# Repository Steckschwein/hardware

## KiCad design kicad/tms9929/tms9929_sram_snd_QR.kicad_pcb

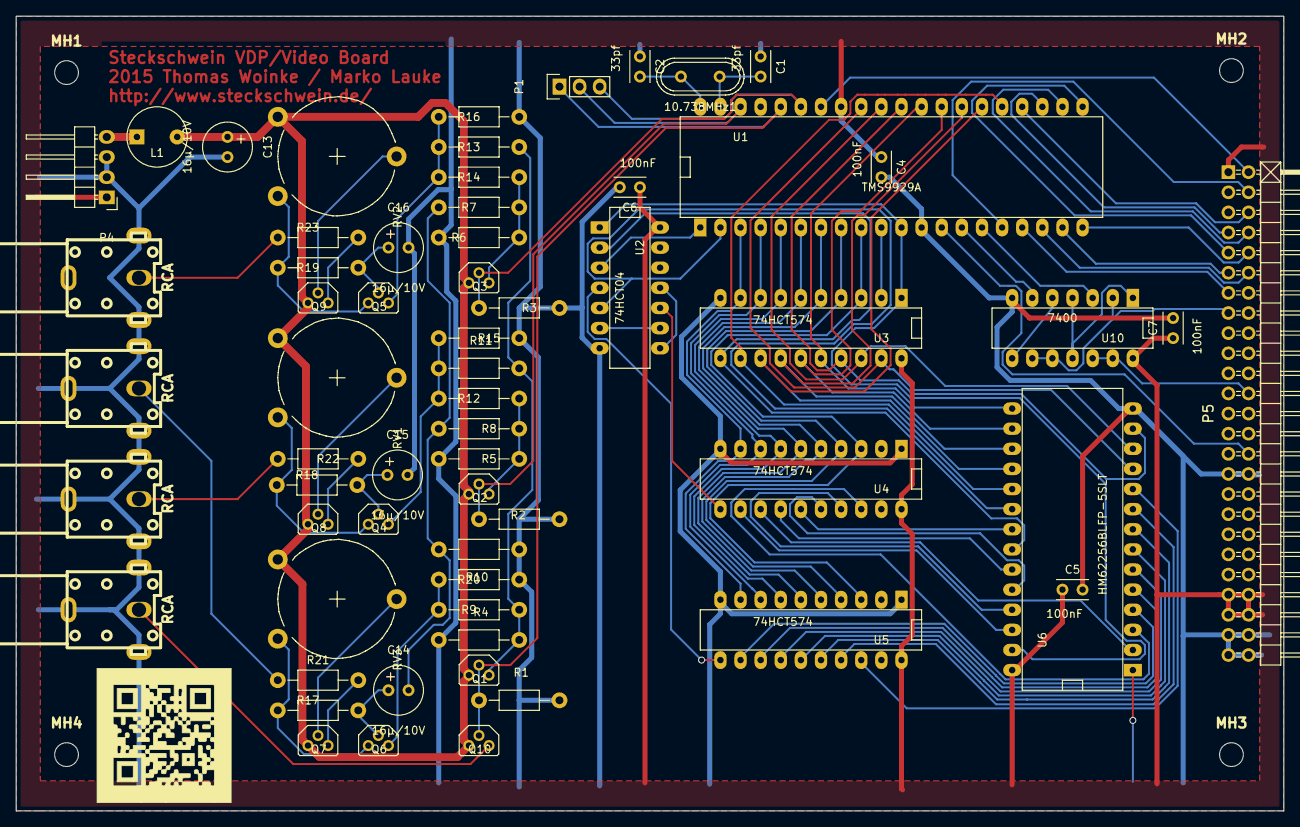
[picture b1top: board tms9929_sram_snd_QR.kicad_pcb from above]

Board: 2 copper layers, 160.0 x 100.3 mm, 66 parts (0 on the bottom side), 87 nets.

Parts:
10.738MHz1: CRYSTAL; Crystal_HC49-U_Vertical
Blue1: RCA; rca_black
C1, C2: 33pf; Capacitor4x3RM2.5
C4, C5, C6, C7: 100nF; Capacitor4x3RM2.5
C13, C14, C15, C16: 16µ/10V; Elko_vert_11.2x6.3mm_RM2.5
Green1: RCA; rca_black
L1: 47µH; INDUCTOR_V
MH1, MH2, MH3, MH4: MountingHole_3mm_RevA_Date21Jun2010; MountingHole_3mm
P1: CONN_01X03; Pin_Header_Straight_1x03
P4: Power; Pin_Header_Angled_1x04
P5: CONN_02X25; Pin_Header_Angled_2x25
Q1, Q2, Q3, Q4, Q5, Q6, Q7, Q8, Q9, Q10: BC550; TO92PN
R1, R2, R3: 470; Resistor_Horizontal_RM10mm
R4, R5, R6: 1K; Resistor_Horizontal_RM10mm
R7, R8, R9, R10, R11, R12, R13, R14, R15, R16, R20: 1K 1%; Resistor_Horizontal_RM10mm
R17, R18, R19: 100K; Resistor_Horizontal_RM10mm
R21, R22, R23: 100; Resistor_Horizontal_RM10mm
RV1, RV2, RV3: 5K; Potentiometer_Trimmer-Piher_PT15-V15_horizontal
Red1: RCA; rca_black
Sync1: RCA; rca_black
U1: TMS9929A; DIP-40__600_ELL
U2: 74HCT04; DIP-14__300_ELL
U3, U4, U5: 74HCT574; DIP-20__300_ELL
U6: HM62256BLFP-5SLT; DIP-28__600_ELL
U10: 7400; DIP-14__300_ELL

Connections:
+12V: L1.1, P4.4
/12VS: C13.1, L1.2, Q1.1, Q2.1, Q3.1, Q7.1, Q8.1, Q9.1, Q10.1, RV1.1, RV2.1, RV3.1
/50Pin/A0: P5.30, U1.13
/50Pin/D0: P5.13, U1.17
/50Pin/D1: P5.12, U1.18
/50Pin/D2: P5.11, U1.19
/50Pin/D3: P5.10, U1.20
/50Pin/D4: P5.9, U1.21
/50Pin/D5: P5.8, U1.22
/50Pin/D6: P5.7, U1.23
/50Pin/D7: P5.6, U1.24
/A0: U5.18, U6.10
/A1: U5.17, U6.9
/A2: U5.16, U6.8
/A3: U5.15, U6.7
/A4: U5.14, U6.6
/A5: U5.13, U6.5
/A6: U5.12, U6.4
/A7: U4.18, U6.3
/A8: U4.17, U6.25
/A9: U4.16, U6.24
/A10: U4.15, U6.21
/A11: U4.14, U6.23
/A12: U4.13, U6.2
/A13: U4.12, U6.26
/AD0: U1.10, U3.2
/AD1: U1.9, U3.3, U4.3, U5.3
/AD2: U1.8, U3.4, U4.4, U5.4
/AD3: U1.7, U3.5, U4.5, U5.5
/AD4: U1.6, U3.6, U4.6, U5.6
/AD5: U1.5, U3.7, U4.7, U5.7
/AD6: U1.4, U3.8, U4.8, U5.8
/AD7: U1.3, U3.9, U4.9, U5.9
/B-Y: P1.3, Q3.2, R3.1, U1.35
/CAS: U1.2, U2.5, U6.20
/COL: U2.10, U4.11
/CS_VDP: P5.24, U10.12, U10.13
/IRQ: P5.4, U1.16
/R-Y: P1.2, Q2.2, R2.1, U1.38
/RAS: U1.1, U2.3
/RD0: U1.32, U3.19, U6.11
/RD1: U1.31, U3.18, U6.12
/RD2: U1.30, U3.17, U6.13
/RD3: U1.29, U3.16, U6.15
/RD4: U1.28, U3.15, U6.16
/RD5: U1.27, U3.14, U6.17
/RD6: U1.26, U3.13, U6.18
/RD7: U1.25, U3.12, U6.19
/RESET: P5.2, U1.34
/RGB-B: Blue1.2, R23.1
/RGB-G: Green1.2, R21.1
/RGB-R: R22.1, Red1.2
/ROW: U2.4, U5.11
/RW: P5.15, U10.2, U10.9, U10.10
/SYNC: Q10.3, Sync1.2
/V_RW: U1.11, U2.1, U3.1, U6.27
/WR: U2.2, U3.11, U6.22
/Y: P1.1, Q1.2, Q10.2, R1.1, U1.36
GND: Blue1.1, C1.1, C2.1, C4.2, C5.2, C6.2, C7.2, C13.2, C15.2, C16.2, Green1.1, P4.2, P4.3, P5.31, P5.32, P5.35, P5.37, P5.47, P5.48, P5.49, P5.50, R1.2, R2.2, R3.2, R4.1, R5.1, R6.1, R10.1, R15.1, R16.1, R20.1, Red1.1, Sync1.1, U1.12, U2.7, U3.10, U4.1, U4.10, U5.1, U5.10, U6.1, U6.14, U10.7
unnamed: 10.738MHz1.1, C1.2, U1.39
unnamed: 10.738MHz1.2, C2.2, U1.40
unnamed: C14.1, Q6.2, R17.2
unnamed: C14.2, R7.1, R8.1, R10.2
unnamed: C15.1, Q4.2, R18.1
unnamed: C16.1, Q5.2, R19.1
unnamed: Q1.3, R4.2, R9.2, R11.2, R13.2
unnamed: Q2.3, R5.2, R8.2, R12.2
unnamed: Q3.3, R6.2, R7.2, R14.2
unnamed: Q4.1, R18.2, RV1.3
unnamed: Q4.3, R11.1, R12.1, R15.2
unnamed: Q5.1, R19.2, RV2.3
unnamed: Q5.3, R13.1, R14.1, R16.2
unnamed: Q6.1, R17.1, RV3.3
unnamed: Q6.3, R9.1, R20.2
unnamed: Q7.2, RV3.2
unnamed: Q7.3, R21.2
unnamed: Q8.2, RV1.2
unnamed: Q8.3, R22.2
unnamed: Q9.2, RV2.2
unnamed: Q9.3, R23.2
unnamed: U1.14, U10.6
unnamed: U1.15, U10.3
unnamed: U2.6, U2.9
unnamed: U2.8, U2.11
unnamed: U10.1, U10.4, U10.11
unnamed: U10.5, U10.8
VCC: C4.1, C5.1, C6.1, C7.1, P4.1, P5.1, P5.43, P5.44, P5.45, P5.46, U1.33, U2.14, U3.20, U4.20, U5.20, U6.28, U10.14

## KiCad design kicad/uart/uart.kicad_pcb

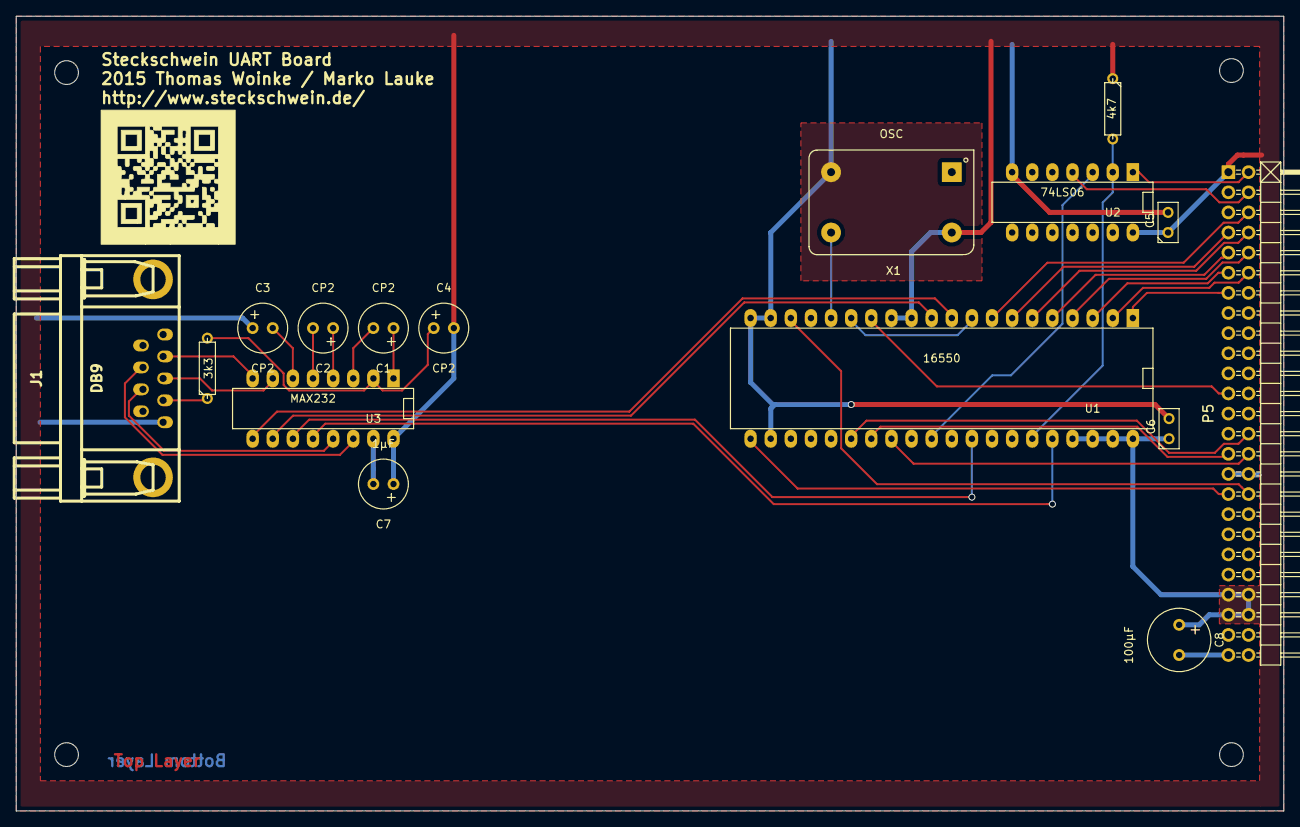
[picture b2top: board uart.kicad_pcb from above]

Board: 2 copper layers, 160.0 x 100.3 mm, 20 parts (0 on the bottom side), 37 nets.

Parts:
C1, C2, C3, C4: CP2; Elko_vert_11.2x6.3mm_RM2.5_CopperClear
C5, C6: 100nF; C1
C7: 1µF; Elko_vert_11.2x6.3mm_RM2.5_CopperClear
C8: 100µF; Elko_vert_11.5x8mm_RM3.5
J1: DB9; DB_9M
MH1, MH2, MH3, MH4: MountingHole_3mm_RevA_Date21Jun2010; MountingHole_3mm
P5: CONN_02X25; Pin_Header_Angled_2x25
R1: 4k7; R3
R2: 3k3; R3
U1: 16550; DIP-40__600_ELL
U2: 74LS06; DIP-14__300_ELL
U3: MAX232; DIP-16__300_ELL
X1: OSC; OSCILLATOR_KXO-200_LargePads

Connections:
/CS_UART: P5.23, U1.14
/Connector/A0: P5.30, U1.28
/Connector/A1: P5.29, U1.27
/Connector/A2: P5.28, U1.26
/Connector/D0: P5.13, U1.1
/Connector/D1: P5.12, U1.2
/Connector/D2: P5.11, U1.3
/Connector/D3: P5.10, U1.4
/Connector/D4: P5.9, U1.5
/Connector/D5: P5.8, U1.6
/Connector/D6: P5.7, U1.7
/Connector/D7: P5.6, U1.8
/IRQ: P5.4, U2.4
/OE: P5.33, U1.21
/RESET: P5.2, U2.1
/WE: P5.34, U1.18
GND: C3.1, C5.2, C6.2, C7.2, C8.2, J1.5, P5.31, P5.32, P5.47, P5.48, P5.49, P5.50, U1.19, U1.20, U1.22, U2.7, U3.15, X1.7
unnamed: C1.1, U3.1
unnamed: C1.2, U3.3
unnamed: C2.1, U3.4
unnamed: C2.2, U3.5
unnamed: C3.2, U3.6
unnamed: C4.1, R2.2, U3.2
unnamed: J1.2, U3.8
unnamed: J1.3, U3.7
unnamed: J1.4, R2.1
unnamed: J1.7, U3.14
unnamed: J1.8, U3.13
unnamed: R1.2, U1.35, U2.2
unnamed: U1.10, U3.9
unnamed: U1.11, U3.10
unnamed: U1.9, U1.15
unnamed: U1.16, X1.8
unnamed: U1.30, U2.3
unnamed: U1.32, U3.11
unnamed: U1.36, U3.12
VCC: C4.2, C5.1, C6.1, C7.1, C8.1, P5.1, P5.43, P5.44, P5.45, P5.46, R1.1, U1.12, U1.13, U1.37, U1.38, U1.39, U1.40, U2.14, U3.16, X1.14
